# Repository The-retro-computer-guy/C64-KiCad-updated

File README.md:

# The C64 250407 replica

A replica of the Commodore 64 250407 1983 mother board, and the schematics.

The replica project was started by Michael K. (Der Alte Bastler) in 2019 to learn SprintLayout, and the process of reverse engineering PCB. I finished the layout in SprintLayout, and imported it to KiCad. The KU motherboard schematics is nowhere to be found on the internet. I used the 250407 Reb.B schematics as reference and modified it to match the KU motherboard layout.

The board has been prototyped, and tested by me and Langwell Cowan.

We are not the first to reverse engineer this board, but we are the first to share the design files online.

# BOM

Please see the [BOM file](250407_bom.csv).

Note that some values were left blank because they depend on the clock circuit (PAL/NTSC), and PLA model. They never made it into the schematics. You can find them in a table to the right of the schematics for 250407.
http://www.zimmers.net/anonftp/pub/cbm/schematics/computers/c64/index.html

# Interactive-BOM

[The interactive bom html page](https://htmlpreview.github.io/?https://raw.githubusercontent.com/bwack/C64-250407-Replica-KiCad/main/interactive-bom/ibom.html) is useful for assembling the board and finding signal traces by using a web browser. Try it here. For a BOM for ordering parts see the BOM above.

# Schematics

Download the PDF file [250407_.pdf](250407_.pdf) for a high quality schematics.
Checkout [this tweet](https://twitter.com/paulrickards/status/1371988589974847492) by Paul Rickards where he plots the KU motherboard schematics KU-14194HB :-)

# Change log
- 2025-06-09: PCB and Schematics V1.3: PAL-NTSC jumpers fox. Thank you, Fred Sauer!
Note: V1.3 was opened and saved in KiCAD 9.0.1. I've verified the new gerbers. Things to beware of I you want to modify the design: 1. If you try to load changes from schematic into the PCBNew, KiCAD will require you to annotate the schematics, which in turn will replace all the resistor array sub parts. Example R1A will become R1A1, which will turn into new parts in PCBNew. Therefore I have not done that in this update. I have only changed the silkscreen, and I have only edited the schematics. 2. KiCAD will ask you to refill the zone fills. I have not done that because it also warns you about some change in fill-constrains. I don't remember exactly what, but I did not refill the fill zones when going to V1.3.
- 2022-08-18: Schematics V1.2: symbol and ERC fixes (Pull request from Gabriele Gorla/GGLABS)
- 2020-06-19: PCB and schematics V1.1: First release
- 2020-04-22: PCB and schematics V1.0: Prototype

# YouTube

Part 1-4:

# License and Disclaimer

Copyright Bwack 2025

This documentation describes Open Hardware and is licensed under the CERN OHL v. 1.2.

You may redistribute and modify this documentation under the terms of theCERN OHL v.1.2. (http://ohwr.org/cernohl). This documentation is distributed WITHOUT ANY EXPRESS OR IMPLIED WARRANTY, INCLUDING OF MERCHANTABILITY, SATISFACTORY QUALITY AND FITNESS FOR APARTICULAR PURPOSE. Please see the CERN OHL v.1.2 for applicable conditions.

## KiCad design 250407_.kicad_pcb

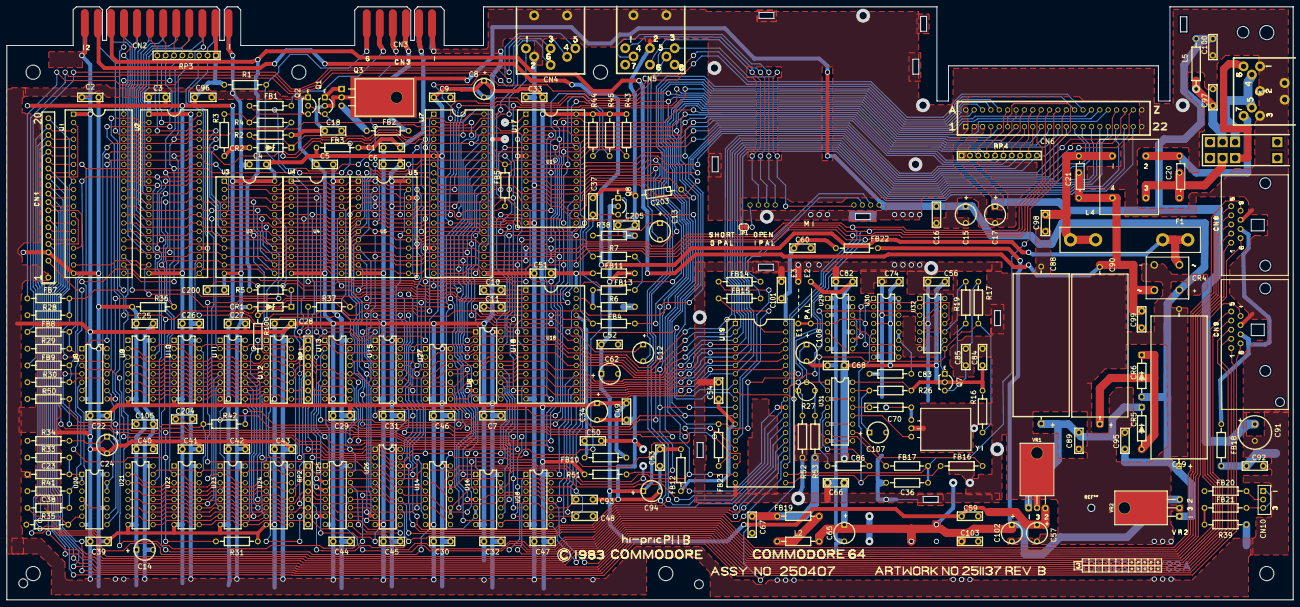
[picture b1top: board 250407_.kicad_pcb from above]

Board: 2 copper layers, 390.0 x 179.8 mm, 215 parts (0 on the bottom side), 227 nets.

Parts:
C1, C2, C3, C4, C5, C6, C7, C9, C16, C18, C22, C25, C26, C27, C28, C29, C30, C31, C32, C33, C39, C40, C41, C42, C43, C44, C45, C46, C47, C49, C50, C51, C52, C53, C54, C56, C59, C60, C66, C67, C68, C74, C82, C84, C89, C92, C95, C96, C98, C99, C101, C103, C105, C200: .1; CAP_P5.08mm
C8, C12, C13, C14, C15, C17, C24, C34, C57, C62, C65, C94, C102, C107, C108: 10uF; CAP_ELYT_RADIAL_P5.08mm_SMALL_RING
C10, C11: 470pF; CAP_P5.08mm
C19: 2200uF; LARGE_ELECTROLYTIC_AXIAL_TH
C20, C21: .22; CAP_POLY_100V_TH_P5.08_and_P12.07mm
C23: 360pF; CAP_AXIAL_P12.7mm
C36: 20pF; RESISTOR
C37: 1000pF; CAP_P5.08mm
C38: 51pF; CAP_AXIAL_P12.7mm
C48, C93: 1800pF; CAP_P5.08mm
C70: 15pF 5%; RESISTOR
C83, C86: 82pF; RESISTOR
C85: .47; CAP_P5.08mm
C88: 1000uF; LARGE_ELECTROLYTIC_AXIAL_TH
C90: 470uF; LARGE_ELECTROLYTIC_AXIAL_TH
C91: 100uF; CAP_ELYT_RADIAL_P5.08mm
C97, C100: .22; CAP_P5.08mm
C203: 82pF; CAPACITOR_RADIAL_P13.97_L9.9_D3.6
C204: NC; CAP_P5.08mm
C205: 220pF; CAP_P5.08mm
CN1: KEYBOARD_20PIN_MALE; KEYBOARD_CON
CN2: USER_PORT_CON; EDGE_CON_24P
CN3: CASSETTE_PORT_CON; EDGE_CON_12P_TAPE
CN4: SERIAL_BUS_CON; SERIAL_CON_DIN6
CN5: AV_CONN; AV_CON_DIN8
CN6: EXPANSION_PORT
CN7: POWER_CON; POWER_CON_D7_250407
CN8, CN9: CONTROL_PORT; JOYPORT_DB9
CN10: LED_CONNECTOR; LED_CON
CR1: IN4371; ZENER_12.7mm
CR2: IN755; ZENER_12.7mm
CR4: BRIDGE_RECTIFIER
CR5, CR6: 1N4001; RECTIFIER_TH_P12.7mm
E2: JUMPER_WIRE_DASHED; JUMPER_WIRE
E3: JUMPER_WIRE
F1: 1A; FUSE
FB1, FB2, FB3, FB4, FB5, FB7, FB8, FB9, FB10, FB11, FB12, FB13, FB14, FB15, FB16, FB17, FB18, FB19, FB20, FB21, FB22, FB23: FERRITE_BEAD; FERRITE_BEAD_TH_P12.7mm
JP1: Jumper_NC_Small; SolderJumper-2_P1.3mm_Bridged_RoundedPad1.0x1.5mm
L2: 2.2uH; RESISTOR
L4: CHOKE
L5: 1.2uH; INDUCTOR_P15.24mm
M1: MODULATOR_LONGBOARD; MODULATOR_PORT_LONGBOARD
Q1, Q2, Q7, Q8: 2SC1815; Q_NPN_ECB
Q3: TP29B/2SD880; TO-220-3_Horizontal_TabDown_250407
R1, R43, R44, R45: 3K3; RESISTOR
R2, R51: 1.5K; RESISTOR
R3, R7: 10K; RESISTOR
R4, R6, R16, R28, R29, R30, R31, R36, R38, R100: 1K; RESISTOR
R5: 560; RESISTOR
R17, R37: 2K7; RESISTOR
R19: 15K; RESISTOR
R26, R53: 100; RESISTOR
R27: 500; POTMETER
R33, R34: 47K; RESISTOR
R35: 470K; RESISTOR
R39: 390; RESISTOR
R41, R50: 1M; RESISTOR
R42: 82; RESISTOR
R52: 330; RESISTOR
RP1, RP2: 33R isolated; RP_ARRAY_7WAY
RP3: 3K3 Bussed; RP_ARRAY_7WAY
RP4: 3K3 Bussed; RP_ARRAY_9WAY
SW1: POWER_SWITCH
U1: CIA_U1; DIP40
U2: CIA_U2; DIP40
U3, U4: 2364A; DIP24
U5: 2332A; DIP24
U6: 2114; DIP18
U7: 6510_MPU; DIP40
U8: 7406N; DIP14
U9, U10, U11, U12, U21, U22, U23, U24: 4164-2; DIP16
U13, U25: 74LS257; DIP16
U14: 74LS258; DIP16
U15: 74LS139; DIP16
U16, U28: 4066_U28; DIP14
U17: PLA_U17; DIP28
U18: 6581; DIP28
U19: VIC; DIP40
U20: 556; DIP14
U26: 74LS373; DIP20
U27: 7408_U27; DIP14
U29: 74LS74; DIP14
U30: 74LS193; DIP16
U31: 74LS629N; DIP16
U32: MC4044; DIP14
VR1: 7812; VREG_TO-220-3_Horizontal_TabDown
VR2: 7805; VREG_TO-220-3_Horizontal_TabDown
Y1: Crystal; CRYSTAL

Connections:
+5V: C2.1, C3.2, C4.2, C5.2, C6.2, C7.1, C8.1, C9.1, C14.1, C17.1, C22.1, C25.1, C26.1, C27.1, C28.1, C29.2, C30.1, C31.2, C32.2, C33.1, C34.1, C39.2, C40.1, C41.1, C42.1, C43.1, C44.2, C45.1, C46.1, C47.1, C49.1, C91.1, C92.1, C96.2, C100.2, CN1.4, CN2.2, CN6.2, CN6.3, FB3.2, FB10.2, FB18.1, L5.1, R1.1, R28.2, R29.2, R30.2, R31.2, R33.1, R34.1, R35.1, R36.1, R39.1, R41.1, R43.1, R44.1, R45.1, R50.1, R51.2, RP3.1, RP4.1, U1.20, U2.20, U3.24, U4.24, U5.21, U5.24, U6.18, U7.6, U8.14, U9.8, U10.8, U11.8, U12.8, U13.16, U14.16, U15.16, U16.14, U17.28, U20.4, U20.10, U20.14, U21.8, U22.8, U23.8, U24.8, U25.16, U26.20, U27.1, U27.14, U28.14
+9V_UNREG: C15.1, C16.1, C18.1, C19.1, C95.1, CR4.1, CR6.2, M1.1, Q1.2, Q3.2, R2.1, VR2.1
+12V: C52.1, C53.1, C57.1, C59.1, C62.1, C94.1, FB11.2, FB12.2, Q8.2, VR1.2
/5V_FB3: C1.1, CN3.B,2, FB3.1
/5V_joyport: CN8.7, CN9.7, FB18.2
/9VAC: C20.2, L4.3, SW1.1
/9VAC~: C21.2, C90.2, C99.2, CN2.10, CR4.4, L4.4, R5.1
/60Hz: R37.2, U1.19, U2.19, U27.3
/250407_sheet2/AEC: U8.3, U14.15, U16.5, U16.6, U16.12, U16.13, U19.16, U26.1, U27.4, U27.12
/250407_sheet2/AUDIO_IN: C12.2, CN5.5
/250407_sheet2/AUDIO_OUT: C13.2, CN5.3, M1.4
/250407_sheet2/BA: CN6.12, U17.26, U19.12, U27.9
/250407_sheet2/CHROMA: FB14.2, M1.3
/250407_sheet2/CHROMA_O: CN5.6, M1.7
/250407_sheet2/COMP_O: CN5.4, M1.5
/250407_sheet2/GR\~W: U6.10, U17.13
/250407_sheet2/LUMA: FB15.2, M1.2
/250407_sheet2/LUMA_O: CN5.1, M1.6
/250407_sheet2/MA0: RP2.4, U9.5, U10.5, U11.5, U12.5, U21.5, U22.5, U23.5, U24.5
/250407_sheet2/MA1: RP2.8, U9.7, U10.7, U11.7, U12.7, U21.7, U22.7, U23.7, U24.7
/250407_sheet2/MA2: RP2.6, U9.6, U10.6, U11.6, U12.6, U21.6, U22.6, U23.6, U24.6
/250407_sheet2/MA3: RP2.2, U9.12, U10.12, U11.12, U12.12, U21.12, U22.12, U23.12, U24.12
/250407_sheet2/MA4: RP1.4, U9.11, U10.11, U11.11, U12.11, U21.11, U22.11, U23.11, U24.11
/250407_sheet2/MA5: RP1.6, U9.10, U10.10, U11.10, U12.10, U21.10, U22.10, U23.10, U24.10
/250407_sheet2/MA6: RP1.2, U9.13, U10.13, U11.13, U12.13, U21.13, U22.13, U23.13, U24.13
/250407_sheet2/MA7: RP1.8, U9.9, U10.9, U11.9, U12.9, U21.9, U22.9, U23.9, U24.9
/250407_sheet2/VA0: RP2.3, U19.24, U25.12, U26.7
/250407_sheet2/VA1: RP2.7, U19.25, U25.9, U26.13
/250407_sheet2/VA2: RP2.5, U19.26, U25.7, U26.8
/250407_sheet2/VA3: RP2.1, U19.27, U25.4, U26.14
/250407_sheet2/VA4: RP1.3, U13.12, U17.20, U19.28, U26.17
/250407_sheet2/VA5: RP1.5, U13.7, U17.21, U19.29, U26.18
/250407_sheet2/VA6: RP1.1, U13.4, U14.4, U26.4
/250407_sheet2/VA6': U14.13, U14.14, U19.30
/250407_sheet2/VA7: RP1.7, U13.9, U14.7, U26.3
/250407_sheet2/VA7': U14.10, U14.11, U19.31
/250407_sheet2/~AEC: R31.1, U8.4, U13.15, U17.25, U25.15
/250407_sheet2/~BASIC: U3.20, U17.17
/250407_sheet2/~CASRAM: R42.2, U17.18
/250407_sheet2/~CASRAM': C204.2, R42.1, U9.15, U10.15, U11.15, U12.15, U21.15, U22.15, U23.15, U24.15
/250407_sheet2/~CAS: C203.2, U13.1, U14.1, U17.9, U19.19, U25.1
/250407_sheet2/~CHAROM: U5.20, U17.15
/250407_sheet2/~CIAS: U15.7, U15.15
/250407_sheet2/~COLOR: U15.6, U27.13
/250407_sheet2/~DMA: CN6.13, RP4.10, U27.5, U27.10
/250407_sheet2/~EXROM: CN6.9, RP4.9, U17.23
/250407_sheet2/~GAME: CN6.8, RP4.7, U17.22
/250407_sheet2/~I\O: U15.1, U17.12
/250407_sheet2/~KERNAL: U4.20, U17.16
/250407_sheet2/~RAS: U9.4, U10.4, U11.4, U12.4, U19.18, U21.4, U22.4, U23.4, U24.4, U26.11
/250407_sheet2/~RESET': CN6.C, FB4.1
/250407_sheet2/~ROMH: CN6.B, U17.10
/250407_sheet2/~ROML: CN6.11, U17.11
/250407_sheet2/~SID: U15.5, U18.8
/250407_sheet2/~VIC: U15.4, U19.10
/'9VAC~: CN2.11, CR4.2, F1.1
/+Vc: C56.1, C67.1, C68.1, C74.1, C82.1, C84.1, E2.1, FB19.2, Q7.2, R16.1, R26.1, R53.1, U29.10, U29.13, U29.14, U30.4, U30.15, U30.16, U31.16, U32.14
/ATN: CN4.3, FB7.1
/ATN': CN2.9, FB7.2, R28.1, U8.12
/ATN_OUT: U2.5, U8.13
/BTNB: CN1.16, CN8.6, U1.6
/CASS_MOTOR: R4.2, U7.24
/CASS_PWR: CN3.C,3, FB2.1
/CASS_RD: CN3.D,4, CN4.1, RP3.4, U1.24
/CASS_SENSE: CN3.F,6, R1.2, U7.25
/CASS_WRT: FB1.2, U7.26
/CASS_WRT': CN3.E,5, FB1.1
/CLK: CN4.4, FB9.1
/CLK': FB9.2, R30.1, U2.8, U8.10
/CLK_OUT: U2.6, U8.11
/CNT1: CN2.4, RP3.5, U1.40
/CNT2: CN2.6, RP3.7, U2.40
/COL0: CN1.13, CN8.1, U1.2
/COL1: CN1.19, CN8.2, U1.3
/COL2: CN1.18, CN8.3, U1.4
/COL3: CN1.17, CN8.4, U1.5
/COL5: CN1.15, U1.7
/COL6: CN1.14, U1.8, U28.6, U28.12
/COL7: CN1.20, U1.9, U28.5, U28.13
/DATA: CN4.5, FB8.1
/DATA': FB8.2, R29.1, U2.9, U8.2
/DATA_OUT: U2.7, U8.1
/F_DIV: U29.11, U30.6
/GND_LED: CN10.2, FB20.2
/JOYA0: CN1.12, CN9.1, U1.10
/JOYA1: CN1.11, CN9.2, U1.11
/JOYA2: CN1.10, CN9.3, U1.12
/JOYA3: CN1.5, CN9.4, U1.13
/LED+: CN10.1, CN10.3, FB21.2
/PA2: CN2.M, U2.4
/PB0: CN2.C, U2.10
/PB1: CN2.D, U2.11
/PB2: CN2.E, U2.12
/PB3: CN2.F, U2.13
/PB4: CN2.H, U2.14
/PB5: CN2.J, U2.15
/PB6: CN2.K, U2.16
/PB7: CN2.L, U2.17
/PH2_FB: FB5.2, U7.39
/POTAX: CN9.9, U28.8
/POTAY: CN9.5, U28.11
/POTBX: CN8.9, U28.1
/POTBY: CN8.5, U28.4
/ROW5: CN1.7, U1.15
/ROW6: CN1.6, U1.16
/ROW7: CN1.9, U1.17
/SP1: CN2.5, RP3.6, U1.39
/SP2: CN2.7, RP3.8, U2.39
/TRIGA: C38.1, R35.2, U20.6
/jumper_select: E2.2, E3.2, U29.4, U30.1, U30.10
/~FLAG2: CN2.B, RP3.2, U2.24
/~PC2: CN2.8, U2.18
/~RESTORE: C38.2, CN1.3, R41.2
A0: CN6.Y, U1.38, U2.38, U3.8, U4.8, U5.8, U6.5, U7.7, U18.9, U25.13, U26.6
A1: CN6.X, U1.37, U2.37, U3.7, U4.7, U5.7, U6.6, U7.8, U18.10, U25.10, U26.12
A2: CN6.W, U1.36, U2.36, U3.6, U4.6, U5.6, U6.7, U7.9, U18.11, U25.6, U26.9
A3: CN6.V, U1.35, U2.35, U3.5, U4.5, U5.5, U6.4, U7.10, U18.12, U25.3, U26.15
A4: CN6.U, U3.4, U4.4, U5.4, U6.3, U7.11, U13.13, U18.13, U26.16
A5: CN6.T, U3.3, U4.3, U5.3, U6.2, U7.12, U13.6, U26.19
A6: CN6.S, U3.2, U4.2, U5.2, U6.1, U7.13, U13.3, U26.5
A7: CN6.R, U3.1, U4.1, U5.1, U6.17, U7.14, U13.10, U26.2
A8: CN6.P, U3.23, U4.23, U5.23, U6.16, U7.15, U15.14, U19.32, U25.14
A9: CN6.N, U3.22, U4.22, U5.22, U6.15, U7.16, U15.13, U19.33, U25.11
A10: CN6.M, U3.19, U4.19, U5.19, U7.17, U15.2, U19.34, U25.5
A11: CN6.L, U3.18, U4.18, U5.18, U7.18, U15.3, U19.23, U25.2
A12: CN6.K, RP4.8, U3.21, U4.21, U7.19, U13.14, U17.27
A13: CN6.J, RP4.6, U7.20, U13.5, U17.2
A14: CN6.H, RP4.5, U7.22, U13.2, U17.3
A15: CN6.F, RP4.4, U7.23, U13.11, U17.4
BTNA\~LP: CN1.8, CN9.6, U1.14, U19.9
CAEC: U7.5, U27.6
CAN+5V: C65.1, C66.1, C102.1, C103.1, FB22.2, L2.1, VR2.2
D0: CN6.21, U1.33, U2.33, U3.9, U4.9, U5.9, U7.37, U16.11, U18.15, U19.7, U21.2, U21.14
D1: CN6.20, U1.32, U2.32, U3.10, U4.10, U5.10, U7.36, U9.2, U9.14, U16.8, U18.16, U19.6
D2: CN6.19, U1.31, U2.31, U3.11, U4.11, U5.11, U7.35, U16.4, U18.17, U19.5, U22.2, U22.14
D3: CN6.18, U1.30, U2.30, U3.13, U4.13, U5.13, U7.34, U10.2, U10.14, U16.1, U18.18, U19.4
D4: CN6.17, U1.29, U2.29, U3.14, U4.14, U5.14, U7.33, U18.19, U19.3, U23.2, U23.14
D5: CN6.16, U1.28, U2.28, U3.15, U4.15, U5.15, U7.32, U11.2, U11.14, U18.20, U19.2
D6: CN6.15, U1.27, U2.27, U3.16, U4.16, U5.16, U7.31, U18.21, U19.1, U24.2, U24.14
D7: CN6.14, U1.26, U2.26, U3.17, U4.17, U5.17, U7.30, U12.2, U12.14, U18.22, U19.39
DOT_CLOCK: C36.1, CN6.6, FB17.2, U19.22
Earth: C1.2, C2.2, C3.1, C4.1, C5.1, C6.1, C7.2, C8.2, C9.2, C14.2, C15.2, C16.2, C17.2, C19.2, C22.2, C23.2, C24.2, C25.2, C26.2, C27.2, C28.2, C29.1, C30.2, C31.1, C32.1, C33.2, C34.2, C36.2, C37.2, C39.1, C40.2, C41.2, C42.2, C43.2, C44.1, C45.2, C46.2, C47.2, C48.2, C49.2, C50.2, C51.2, C52.2, C53.2, C54.2, C56.2, C57.2, C59.2, C60.2, C62.2, C65.2, C66.2, C67.2, C68.2, C74.2, C82.2, C83.2, C84.2, C88.2, C89.2, C91.2, C92.2, C93.2, C94.2, C95.2, C96.1, C97.1, C98.2, C99.1, C100.1, C101.2, C102.2, C103.2, C105.1, C107.2, C108.2, C200.2, C203.1, C204.1, C205.2, CN1.1, CN2.1, CN2.12, CN2.A, CN2.N, CN3.A,1, CN4.2, CN5.2, CN6.1, CN6.22, CN6.A, CN6.Z, CN7.1, CN7.2, CN7.3, CN8.8, CN9.8, CR1.2, CR2.2, CR4.3, E3.1, FB20.1, JP1.2, Q2.1, R3.2, R6.1, R38.1, R52.2, U1.1, U2.1, U3.12, U4.12, U5.12, U6.9, U7.21, U8.7, U9.16, U10.16, U11.16, U12.16, U13.8, U14.8, U15.8, U16.7, U17.14, U17.19, U18.14, U19.20, U20.7, U21.16, U22.16, U23.16, U24.16, U25.8, U26.10, U27.7, U28.7, U29.1, U29.2, U29.3, U29.7, U30.8, U30.14, U31.3, U31.6, U31.8, U31.9, U31.11, U31.14, U32.7, VR1.3, VR2.3, Y1.3
unnamed: C10.1, U18.1
unnamed: C10.2, U18.2
unnamed: C11.1, U18.3
unnamed: C11.2, U18.4
unnamed: C12.1, U18.26
unnamed: C13.1, C205.1, Q8.1, R38.2
unnamed: C18.2, CR2.1, Q1.3, Q2.2, R2.2
unnamed: C20.1, CN7.7, L4.2
unnamed: C21.1, C98.1, F1.2, L4.1
unnamed: C23.1, R33.2, U20.1, U20.2
unnamed: C24.1, R34.2, U20.12, U20.13
unnamed: C37.1, Q8.3, R7.1
unnamed: C50.1, FB10.1, U18.25
unnamed: C51.1, FB11.1, U18.28
unnamed: C54.1, FB12.1, U19.13
unnamed: C70.1, Y1.2
unnamed: C70.2, U31.13
unnamed: C83.1, U30.11, U30.12
unnamed: C85.1, R17.2
unnamed: C85.2, Q7.3, R19.1
unnamed: C86.1, U31.5
unnamed: C86.2, U31.4
unnamed: C88.1, C89.1, CR5.1, VR1.1
unnamed: C90.1, CR5.2, CR6.1
unnamed: C97.2, L5.2, SW1.4
unnamed: C60.1, C101.1, FB22.1, U19.40
unnamed: C105.2, R50.2, U20.8
unnamed: C107.1, R26.2, U31.15
unnamed: C108.1, R27.3, U31.1
unnamed: C200.1, CR1.1, R5.2, R100.1
unnamed: CN6.7, U15.10
unnamed: CN6.10, U15.9
unnamed: CN7.4, CN7.5, SW1.5
unnamed: CN7.6, SW1.2
unnamed: FB2.2, Q3.3
unnamed: FB13.1, R6.2, U18.27
unnamed: FB13.2, R7.2
unnamed: FB14.1, U19.14
unnamed: FB15.1, U19.15
unnamed: FB16.1, U31.10
unnamed: FB17.1, U31.7
unnamed: FB19.1, L2.2
unnamed: FB21.1, R39.2
unnamed: FB23.1, U19.17
unnamed: JP1.1, M1.8
unnamed: Q1.1, Q3.1
unnamed: Q2.3, R3.1, R4.1
unnamed: Q7.1, U32.9
unnamed: R16.2, R17.1, U31.2, U32.8
unnamed: R19.2, U32.5, U32.10
unnamed: R27.1, R53.2
unnamed: R27.2, R52.1
unnamed: R37.1, R100.2, U27.2
unnamed: U14.6, U14.9
unnamed: U14.3, U14.12
unnamed: U6.11, U16.2, U19.35
unnamed: U6.12, U16.3, U19.36
unnamed: U6.13, U16.9, U19.37
unnamed: U6.14, U16.10, U19.38
unnamed: U8.5, U20.5
unnamed: U8.9, U20.9
unnamed: U6.8, U27.11
unnamed: U29.5, U30.9
unnamed: U29.9, U32.1
unnamed: U29.8, U29.12
unnamed: U31.12, Y1.1
unnamed: U32.2, U32.11
unnamed: U32.4, U32.13
PHI0: FB23.2, U7.1, U32.3
PHI2: CN6.E, FB5.1, U1.25, U2.25, U18.6
PHI_COLOR: FB16.2, U19.21, U30.5
POTX: C48.1, U18.24, U28.2, U28.9
POTY: C93.1, U18.23, U28.3, U28.10
RDY: U7.2, U27.8
R\~W: CN6.5, R51.1, U1.22, U2.22, U7.38, U9.3, U10.3, U11.3, U12.3, U17.24, U18.7, U19.11, U21.3, U22.3, U23.3, U24.3
~CHAREN: R43.2, U7.27, U17.6
~CIA1: U1.23, U15.12
~CIA2: U2.23, U15.11
~HIRAM: R44.2, U7.28, U17.7
~IRQ: CN6.4, RP4.3, U1.21, U7.3, U19.8
~LORAM: R45.2, U7.29, U17.8
~NMI: CN6.D, RP3.3, U2.21, U7.4, U8.6
~RESET: CN2.3, CN4.6, FB4.2, R36.2, U1.34, U2.34, U7.40, U8.8, U18.5
~VA14: U2.2, U14.2, U17.5
~VA15: U2.3, U14.5

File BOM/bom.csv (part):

Reference," Quantity"," Value"," Footprint",Mouser P/N,Reichelt P/N,Other
C96 C22 C47 C3 C2 C9 C105 C39 C46 C18 C1 C99 C98 C92 C95 C89 C59 C103 C68 C74 C67 C84 C56 C66 C82 C200 C44 C28 C43 C27 C42 C26 C41 C25 C40 C29 C4 C5 C6 C33 C31 C30 C7 C32 C45 C101 C60 C54 C53 C16 C49 C50 C52 C51,"54",".1","Cap MLCC 0.1uF 50V X7R P5.08mm Radial",80-C322C104K5R5TA or 581-SR215C104KART,X7R-5 100N,
C8 C24 C57 C102 C65 C17 C94 C15 C13 C34 C62 C12 C14 C107 C108,"15","10uF","Cap Alu 10uF 25V 5x5mm P2.5mm Radial",667-ECE-A1EKS100I,M 10U 25,
"C11 C10 ","2","470pF","Cap MLCC 470pF X7R Axial",594-A471K15X7RF5UAA,?,
"C19 ","1","2200uF","Cap Elyt 2200uF 16V 15x30mm Axial",594-2222-021-16222 or 594-2222-021-15222 or 598-228TTA016M,COS 105 2200/16,
"C203 ","1","?","KU-14194HB-RevB-KiCad:CAPACITOR_RADIAL_P13.97_L9.9_D3.6",~,,
"C204 ","1","?","KU-14194HB-RevB-KiCad:CAP_P5.08mm",~,,
"C205 ","1","220pF","KU-14194HB-RevB-KiCad:CAP_P5.08mm",~,,
"C21 C20 ","2",".22","Cap Polyester Film 0.22uF 63VAC P10mm",594-2222-368-25224,MKS4-100 220N2,
"C23 ","1","360pF","Cap MLCC 350pF 50V C0G Axial",594-A331J15C0GF5TAA,?,
"C36 ","1","20pF","Cap MLCC 20pF C0G Axial",581-SA102A200JAR,?,
"C37 ","1","1000pF","KU-14194HB-RevB-KiCad:CAP_P5.08mm",~,,
"C38 ","1","51pF","Cap MLCC 51pF (47pF OK) X7R Axial",581-SA102A470JAR,?,
"C48 C93 ","2","1800pF","Cap MLCC 1800pF X7R Axial",581-SA101C182KAR,?,
"C70 ","1","15pF 5%","Cap MLCC 15pF 50V 5% C0G Axial/Radial Leaded",594-A150J15C0GH5TAA,KERKO 15P,
"C85 ","1",".47","Cap MLCC 0.47uF +80/-20% X7R P5.08mm Radial","80-C330C474K5R or 81-RCER71H474K1K1H3B ",Z5U-5 470N,
"C86 C83 ","2","82pF","Cap MLCC 82pF 100V C0G Axial / Radial Disc",80-C410C820J1G,,
"C88 ","1","1000uF","Cap Elyt 1000uF 16V 20% 10x30mm Axial",594-2222-021-15102 or 598-108TTA016M,,
"C90 ","1","470uF","Cap Elyt 470uF 50V 20% 13x26mm Axial",598-477TTA050M,COS 105 470/50,
"C91 ","1","100uF","Cap Elyt 100uF 16V 20% 6.3x11mm Radial",REA101M1CBK-0611P,FR-A 100U 16,
"C97 C100 ","2",".22","Cap MLCC 0.22uF 50V X7R P5.08mm Radial",80-C330C224K1R,Z5U-5 220N,
"CN1 ","1","KEYBOARD_20PIN_MALE","Pin Header 20 POS P2.54mm male vertical",538-22-28-4204,MPE 087-1-020,
"CN10 ","1","LED_CONNECTOR","Pin Header 3 POS P2.54mm male vertical",538-22-28-4033,RND 205-00624,
"CN2 ","1","USER_PORT_CON","KU-14194HB-RevB-KiCad:EDGE_CON_24P",-,,
"CN3 ","1","CASSETTE_PORT_CON","KU-14194HB-RevB-KiCad:EDGE_CON_12P_TAPE",-,,
"CN4 ","1","SERIAL_BUS_CON","KU-14194HB-RevB-KiCad:SERIAL_CON_DIN6",,,
"CN5 ","1","AV_CONN","KU-14194HB-RevB-KiCad:AV_CON_DIN8",-,,
"CN6 ","1","EXPANSION_PORT","Conn Edge Dual Female 44 POS P2.54mm",,Digikey: H122591-ND,
"CN7 ","1","POWER_CON","KU-14194HB-RevB-KiCad:POWER_CON_D7_250407",,,
"CN8 CN9 ","2","CONTROL_PORT","Standard Connector DSUB E09P RA590",571-5747467-1,,
"CR1 ","1","IN4371","Zener Diode 2.7V 500mW DO-35-2",78-TZX2V7A,"ZF 2,7",
"CR100 CR102 CR101 CR103 ","4","D_Small_ALT",,~,,
"CR2 ","1","IN755","Zener Diode 7.5V 500mW DO-35-2",78-TZX7V5C,"ZF 7,5",
"CR4 ","1","BRIDGE_RECTIFIER","Bridge Rectifier 2A 600V Vf=1.05V",627-S2VB60-5000,KBPC604 DIO,
CR5 CR6,"2","1N4001","Rectifier 1A Vr=50V",625-1N4001-E3/54 or 625-1N4001-E3/53,,
"E1 ","1","JUMPER_WIRE","KU-14194HB-RevB-KiCad:JUMPER_WIRE",-,,
"E2 ","1","JUMPER_WIRE_DASHED","KU-14194HB-RevB-KiCad:JUMPER_WIRE",-,,
"F1 ","2","1A","Fuse Clips (buy two)",504-BK/1A1907-03-R,,
"FB18 FB4 FB22 FB12 FB14 FB15 FB13 FB10 FB11 ","9","FERRITE_BEAD","Ferrite Bead D3.5 L4.45mm Axial",623-2743001112LF or 81-BL01RN1A2A2B,BEAD 8-21,
"FB7 FB9 FB8 FB5 FB2 FB1 FB3 FB20 FB21 FB17 FB16 FB19 FB23 ","13","FERRITE_NARROW","Ferrite Bead D3.5 L4.45mm Axial",623-2743001112LF or 81-BL01RN1A2A2B,BEAD 8-21,
"JP1 ","1","Jumper_NC_Small","Jumper:SolderJumper-2_P1.3mm_Bridged_RoundedPad1.0x1.5mm",~,,
"L2 ","1","2.2uH","Inductor 2.2uH 5% Radial",652-78F2R2J-RC,"L-MICC 2,2µ",
"L4 ","1","CHOKE","Common Mode Choke 250V 3.8mH 2.1A 150mOhms",80-SSR10V-21038,,
"L5 ","1","1.2uH","Inductor 1.5uH 10% Radial",542-5800-4R7-RC,"L-HBCC 1,5µ",
"M1 ","1","MODULATOR_LONGBOARD","KU-14194HB-RevB-KiCad:MODULATOR_PORT_LONGBOARD",-,,
"Q2 Q1 Q7 Q8 ","4","2SC1815","Bipolar Transistor TO-92 Vce=60V 400mA",2SC1815,SC 1815,
"Q3 ","1","TP29B/2SD880","Bipolar Transistor TO-220",512-KSD880YTU,SD 880,
"R1 R43 R44 R45 ","4","3K3","Resistor 3K3 0207 Axial",594-MBB02070C3301FC1,"METALL 3,30K",
R17 R37,"2","2K7","Resistor 2K7 0207 Axial",594-MBB02070C2701FCT,"METALL 2,70K",
"R19 ","1","15K","Resistor 15K 0207 Axial",594-MBB02070C1502FC1,"METALL 15,0K",
"R2 R51 ","2","1.5K","Resistor 1K5 0207 Axial",594-MBB02070C1501FCT,"1W 1,5K",
"R26 R53 ","2","100","Resistor 100 0207 Axial",594-MBB02070C1000FCT,METALL 100,
"R27 ","1","500","Trimmer Resistor 500 Ohms Linear",652-3306F-1-501,BOU 3386P-1-501,
"R28 R30 R29 R36 R4 R16 R100 R31 R38 R6 ","10","1K","Resistor 1K 0207 Axial",594-MBB02070C1001FCT,"METALL 1,00K",
"R3 R7 ","2","10K","Resistor 10K 0207 Axial",594-MBB02070C1002FCT,"METALL 10,0K",
"R33 R34 ","2","47K","Resistor 47K 0207 Axial",594-MBB02070C4702FC1,"METALL 47,0K",
"R35 ","1","470K","Resistor 470K 0207 Axial",594-MBB02070C4703FCT,METALL 470K,
"R39 ","1","390","Resistor 390 0207 Axial",594-MBB02070C3900FCT,METALL 390,
"R41 R50 ","2","1M","Resistor 1M 0207 Axial",594-MBB02070C1004FCT or 603-HHV-25JT-52-1M,,
"R42 ","1","~","KU-14194HB-RevB-KiCad:RESISTOR",-,-,
"R5 ","1","560","Resistor 560 0207 Axial",594-MBB02070C5600FCT,METALL 560,
"R52 ","1","330","Resistor 330 0207 Axial",594-MBB02070C3300FCT,,
"RP1 RP2 ","2","33","Resistor Network 33R Isolated 8 pin SIP",652-4308R-2LF-33 or 268-33-RC,,
"RP3 ","1","R_ARRAY_7WAY_US","Resistor Network 3K3 Bussed 8 pin SIP",774-77081332P,,
"RP4 ","1","R_ARRAY_9WAY_US","Resistor Network 3K3 Bussed 10 pin SIP",774-770101332P,,
"SW1 ","1","POWER_SWITCH","KU-14194HB-RevB-KiCad:POWER_SWITCH",,,
"U1 ","1","CIA_U1","KU-14194HB-RevB-KiCad:DIP40",-,,
"U12 U24 U11 U23 U10 U22 U21 U9 ","8","4164-2","KU-14194HB-RevB-KiCad:DIP16",-,,
"U14 ","1","74LS258","QUADRUPLE 2-LINE TO 1-LINE DATA SELECTORS/MULTIPLEXERS","595-SN74LS258BN ",,
"U15 ","1","74LS139","DUAL 2-LINE TO 4-LINE DECODERS/MULTIPLEXERS","595-SN74LS139AN ",,
"U17 ","1","PLA_U17","KU-14194HB-RevB-KiCad:DIP28",-,,
"U18 ","1","6581","KU-14194HB-RevB-KiCad:DIP28",-,,
"U19 ","1","VIC","KU-14194HB-RevB-KiCad:DIP40",-,,
"U2 ","1","CIA_U2","KU-14194HB-RevB-KiCad:DIP40",-,,
"U20 ","1","556","DUAL PRECISION TIMERS","595-NE556N ",,
"U25 U13 ","2","74LS257","QUADRUPLE 2-LINE TO 1-LINE DATA SELECTORS/MULTIPLEXERS","595-SN74LS257BN ",,
"U26 ","1","74LS373","OCTAL D-TYPE TRANSPARENT LATCHES AND EDGE-TRIGGERED FLIP-FLOPS","595-SN74LS373N ",,
"U27 ","1","7408","QUADRUPLE 2-INPUT POSITIVE-AND GATES","595-SN74LS08N ",,
"U28 U16 ","2","4066","CMOS Quad Bilateral Switch","595-CD4066BE ",,
"U29 ","1","74LS74","DUAL D-TYPE POSITIVE-EDGE-TRIGGERED FLIP-FLOPS WITH PRESET AND CLEAR","595-SN74LS74AN ",,
"U3 U4 ","2","2364A","KU-14194HB-RevB-KiCad:DIP24 BASIC AND KERNAL ROM",-,,
"U30 ","1","74LS193","SYNCHRONOUS 4-BIT UP/DOWN COUNTERS (DUAL CLOCK WITH CLEAR)","595-SN74LS193N ",,
"U31 ","1","74LS629N","VOLTAGE-CONTROLLED OSCILLATORS","595-SN74LS629N ",,
"U32 ","1","MC4044","KU-14194HB-RevB-KiCad:DIP14",-,,
"U5 ","1","2332A","KU-14194HB-RevB-KiCad:DIP24 CHAR ROM",-,,
"U6 ","1","2114","KU-14194HB-RevB-KiCad:DIP18 COLOR RAM",-,,
"U7 ","1","6510_MPU","KU-14194HB-RevB-KiCad:DIP40",-,,
"U8 ","1","7406N","HEX INVERTER BUFFERS/DRIVERSWITH OPEN-COLLECTOR HIGH-VOLTAGE OUTPUTS","595-SN7406N ",,
"VR1 ","1","7812","Linear Voltage Regulators 12V 1A Positive","863-MC7812CTG ",,
"VR2 ","1","7805","Linear Voltage Regulators 5V 1A Positive","863-MC7805CTG ",,
"Y1 ","1","Crystal","Crystals HC49/U","815-AB-17.734475-B4 ",,
,,,,,,
Other:,,,,,,
,"Quantity",,"Description",mouser,,
,"4",,"Socket PDIP 40P P2.54mm W15.24mm DUAL WIPE",517-4840-6000-CP,,
,"2",,"Socket PDIP 28P P2.54mm W15.24mm DUAL WIPE",517-4828-6000-CP,,
,"3",,"Socket PDIP 24P P2.54mm W15.24mm DUAL WIPE",517-4824-6000-CP,,
,"1",,"Socket PDIP 20P P2.54mm W7.62mm DUAL WIPE",517-4820-3000-CP,,
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
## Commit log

2024-07-20 Update README.md
    Fixing of spelling and grammatical errors
2024-07-20 Updated BOM
    This Is a BOM containing all the components available for purchase on mouser.com (Not complete) (some parts still need to be sourced)
2024-07-20 Rename ibom.html to interactive-bom.html
2024-07-20 Rename 250407_bom.csv to BOM/bom.csv
2024-07-20 Rename 250407_.kicad_pcb to KiCad/C64LB.kicad_pcb
2024-07-20 Rename 250407_.pro to KiCad/C64LB.pro
2024-07-20 Rename 250407_-brd.svg to KiCad/C64LB.svg
2025-06-09 V1.3. PAL-NTSC E1 E2 E3 fix. Saved in KiCAD 9.0.1
2026-01-21 Update README.md
    Updated with better English convention and some useful additions.

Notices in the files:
250407_.kicad_pcb:
Licensed under CERN OHL v.1.2
